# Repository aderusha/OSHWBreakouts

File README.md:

# OSHW Breakout Boards

I occasionally have had need for various breakout boards and when I can't find what I'm after I'll design my own and share the results here.

All PCBs have been designed with the excellent [KiCad EDA software](http://kicad.org/) and full source files for every design are included.  All designs are offered under [MIT License](LICENSE).

## Contents

* [8P8C (aka RJ45, Ethernet) breakouts](8P8C)

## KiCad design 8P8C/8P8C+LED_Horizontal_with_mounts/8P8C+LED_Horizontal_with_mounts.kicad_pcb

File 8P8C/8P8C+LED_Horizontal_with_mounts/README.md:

# 8P8C+LED_Horizontal_with_mounts

## *UNTESTED - NOT READY FOR GENERAL USE*

### Amphenol RJHSE-538*x*

The [Amphenol RJHSE-538*x*](https://www.amphenol-icc.com/modular-jacks-rjhse5381.html) (also [RJHSE-L38*x*](https://www.amphenol-icc.com/modular-jacks-rjhsel381.html)) series of shielded 8P8C connectors are horizontally mounted to a PCB and offer 2 LED lights (commonly, green and yellow).  This footprint is widely cloned by Chinese suppliers making for an inexpensive and readily-available solution for prototyping.

This is a breadboard-compatible horizontal 8P8C breakout with mounting screw holes. [[*preview*](MCAD/8P8C+LED_Horizontal_with_mounts-Assembled.stl)]

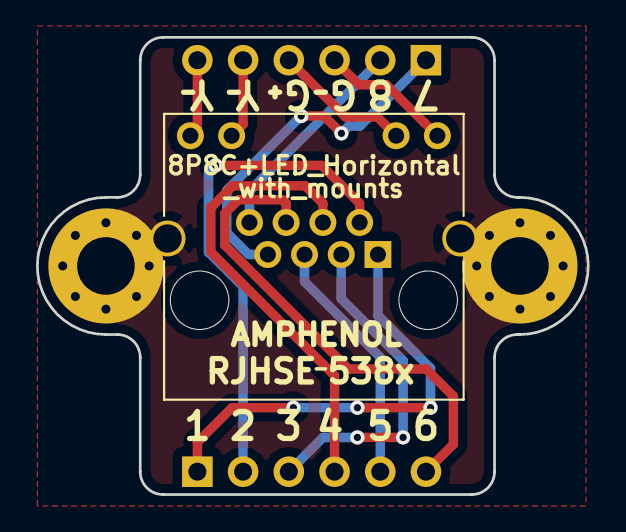
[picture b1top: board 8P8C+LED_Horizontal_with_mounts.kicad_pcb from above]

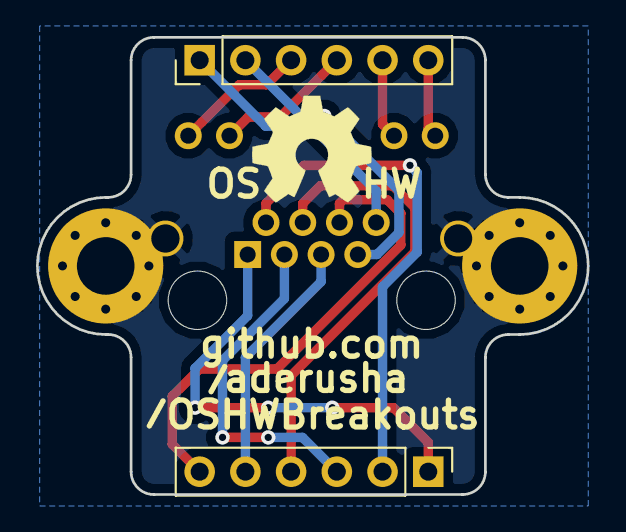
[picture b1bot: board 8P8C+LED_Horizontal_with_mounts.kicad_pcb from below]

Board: 2 copper layers, 30.6 x 25.4 mm, 5 parts (2 on the bottom side), 13 nets.

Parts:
H1, H2: MountingHole_Pad; MountingHole_3.2mm_M3_Pad_Via
J1: 8P8C_LED_Shielded; RJ45_Amphenol_RJHSE538X
J2, J3: Conn_01x06; PinHeader_1x06_P2.54mm_Vertical

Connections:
/G+: J1.10, J3.4
/G-: J1.9, J3.3
/Pin1: J1.1, J2.1
/Pin2: J1.2, J2.2
/Pin3: J1.3, J2.3
/Pin4: J1.4, J2.4
/Pin5: J1.5, J2.5
/Pin6: J1.6, J2.6
/Pin7: J1.7, J3.1
/Pin8: J1.8, J3.2
/Y+: J1.12, J3.6
/Y-: J1.11, J3.5
GND: H1.1, H2.1, J1.SH

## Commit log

2018-12-29 Documentation updates
2018-12-29 VRML export
2018-12-30 Re-align pins
2021-11-09 Update README.md
    https://forum.kicad.info/t/warning-avoid-all-links-to-kicad-pcb-org-use-kicad-org/31521
